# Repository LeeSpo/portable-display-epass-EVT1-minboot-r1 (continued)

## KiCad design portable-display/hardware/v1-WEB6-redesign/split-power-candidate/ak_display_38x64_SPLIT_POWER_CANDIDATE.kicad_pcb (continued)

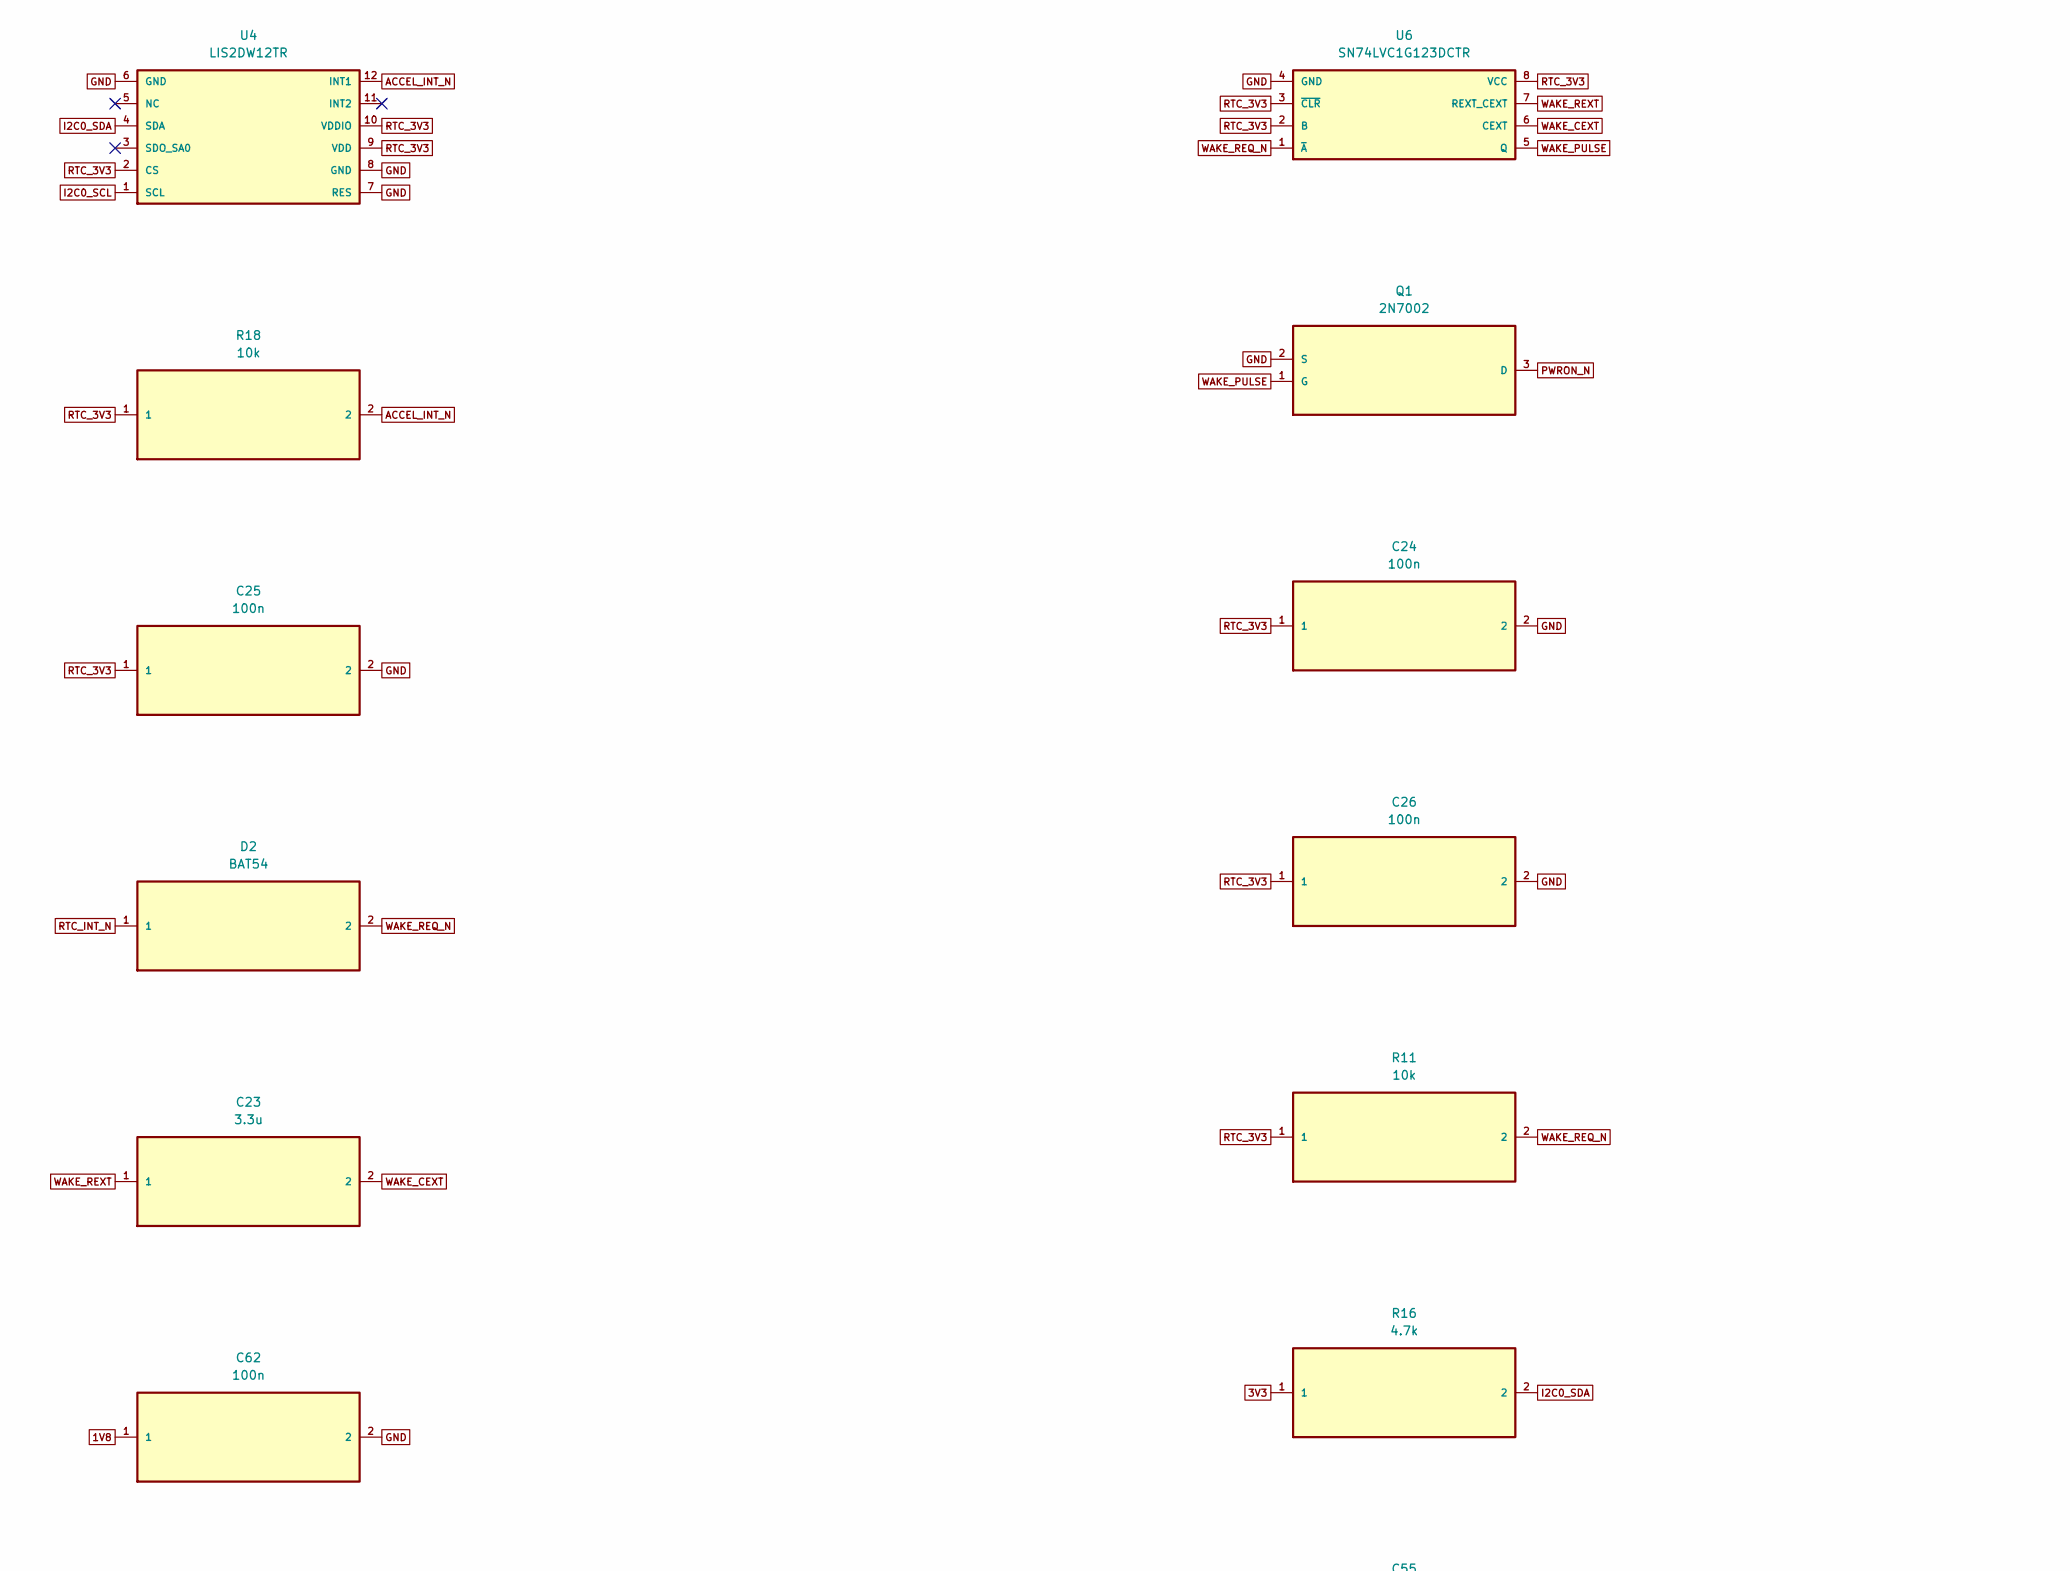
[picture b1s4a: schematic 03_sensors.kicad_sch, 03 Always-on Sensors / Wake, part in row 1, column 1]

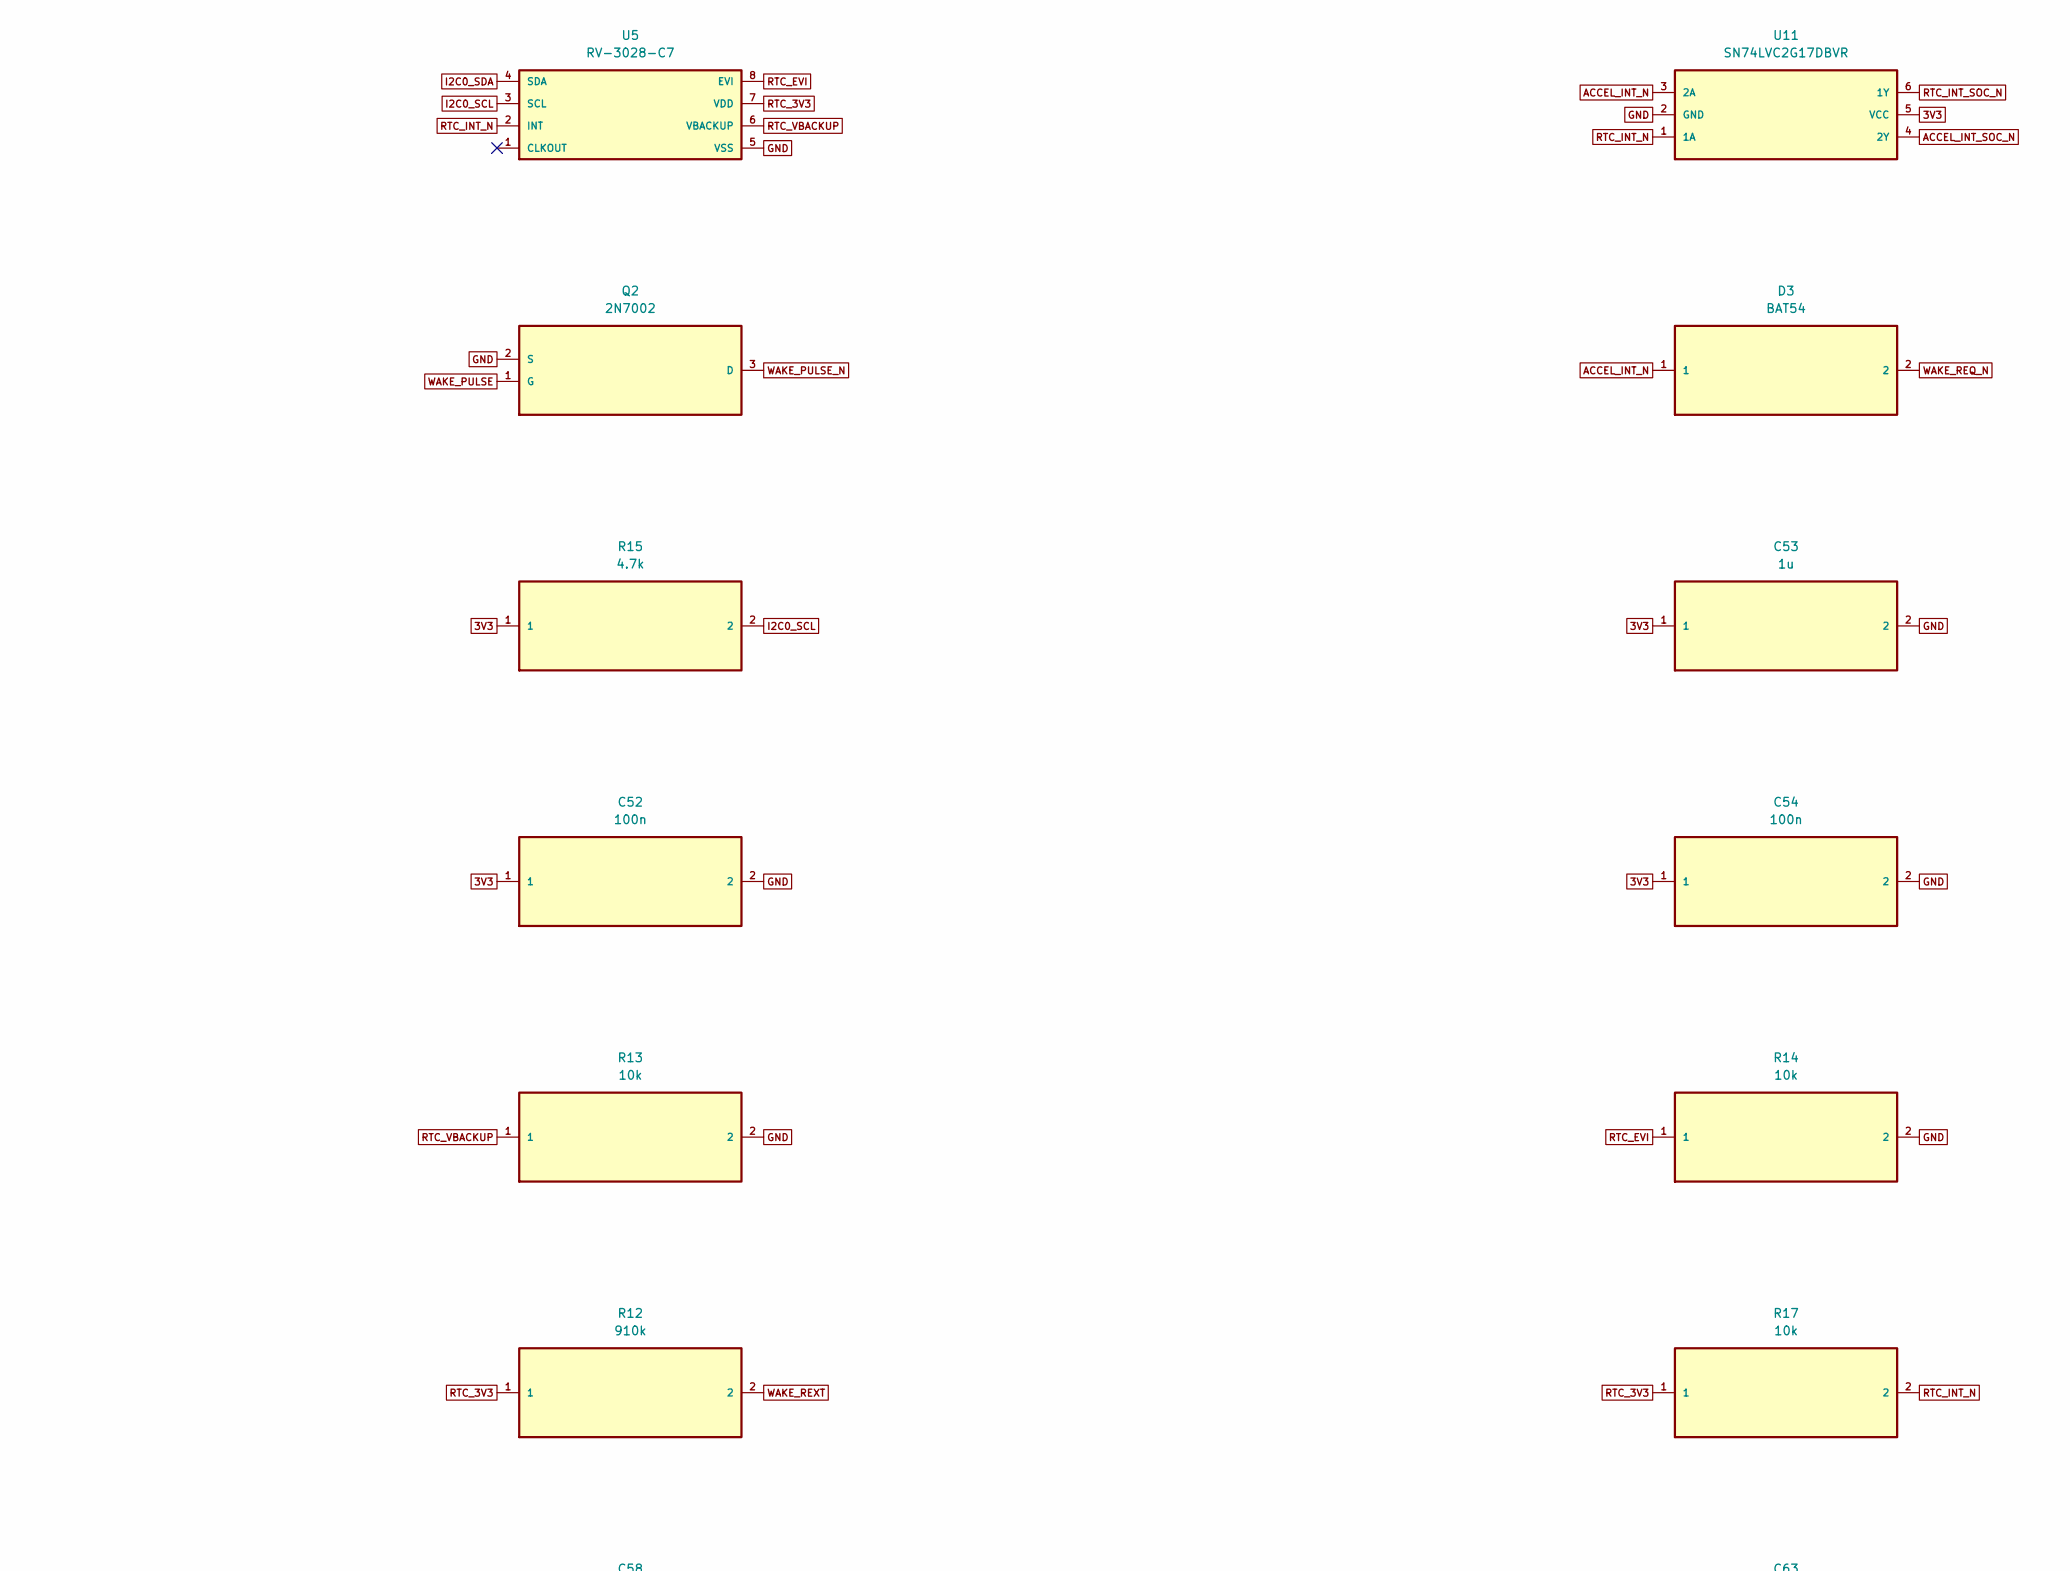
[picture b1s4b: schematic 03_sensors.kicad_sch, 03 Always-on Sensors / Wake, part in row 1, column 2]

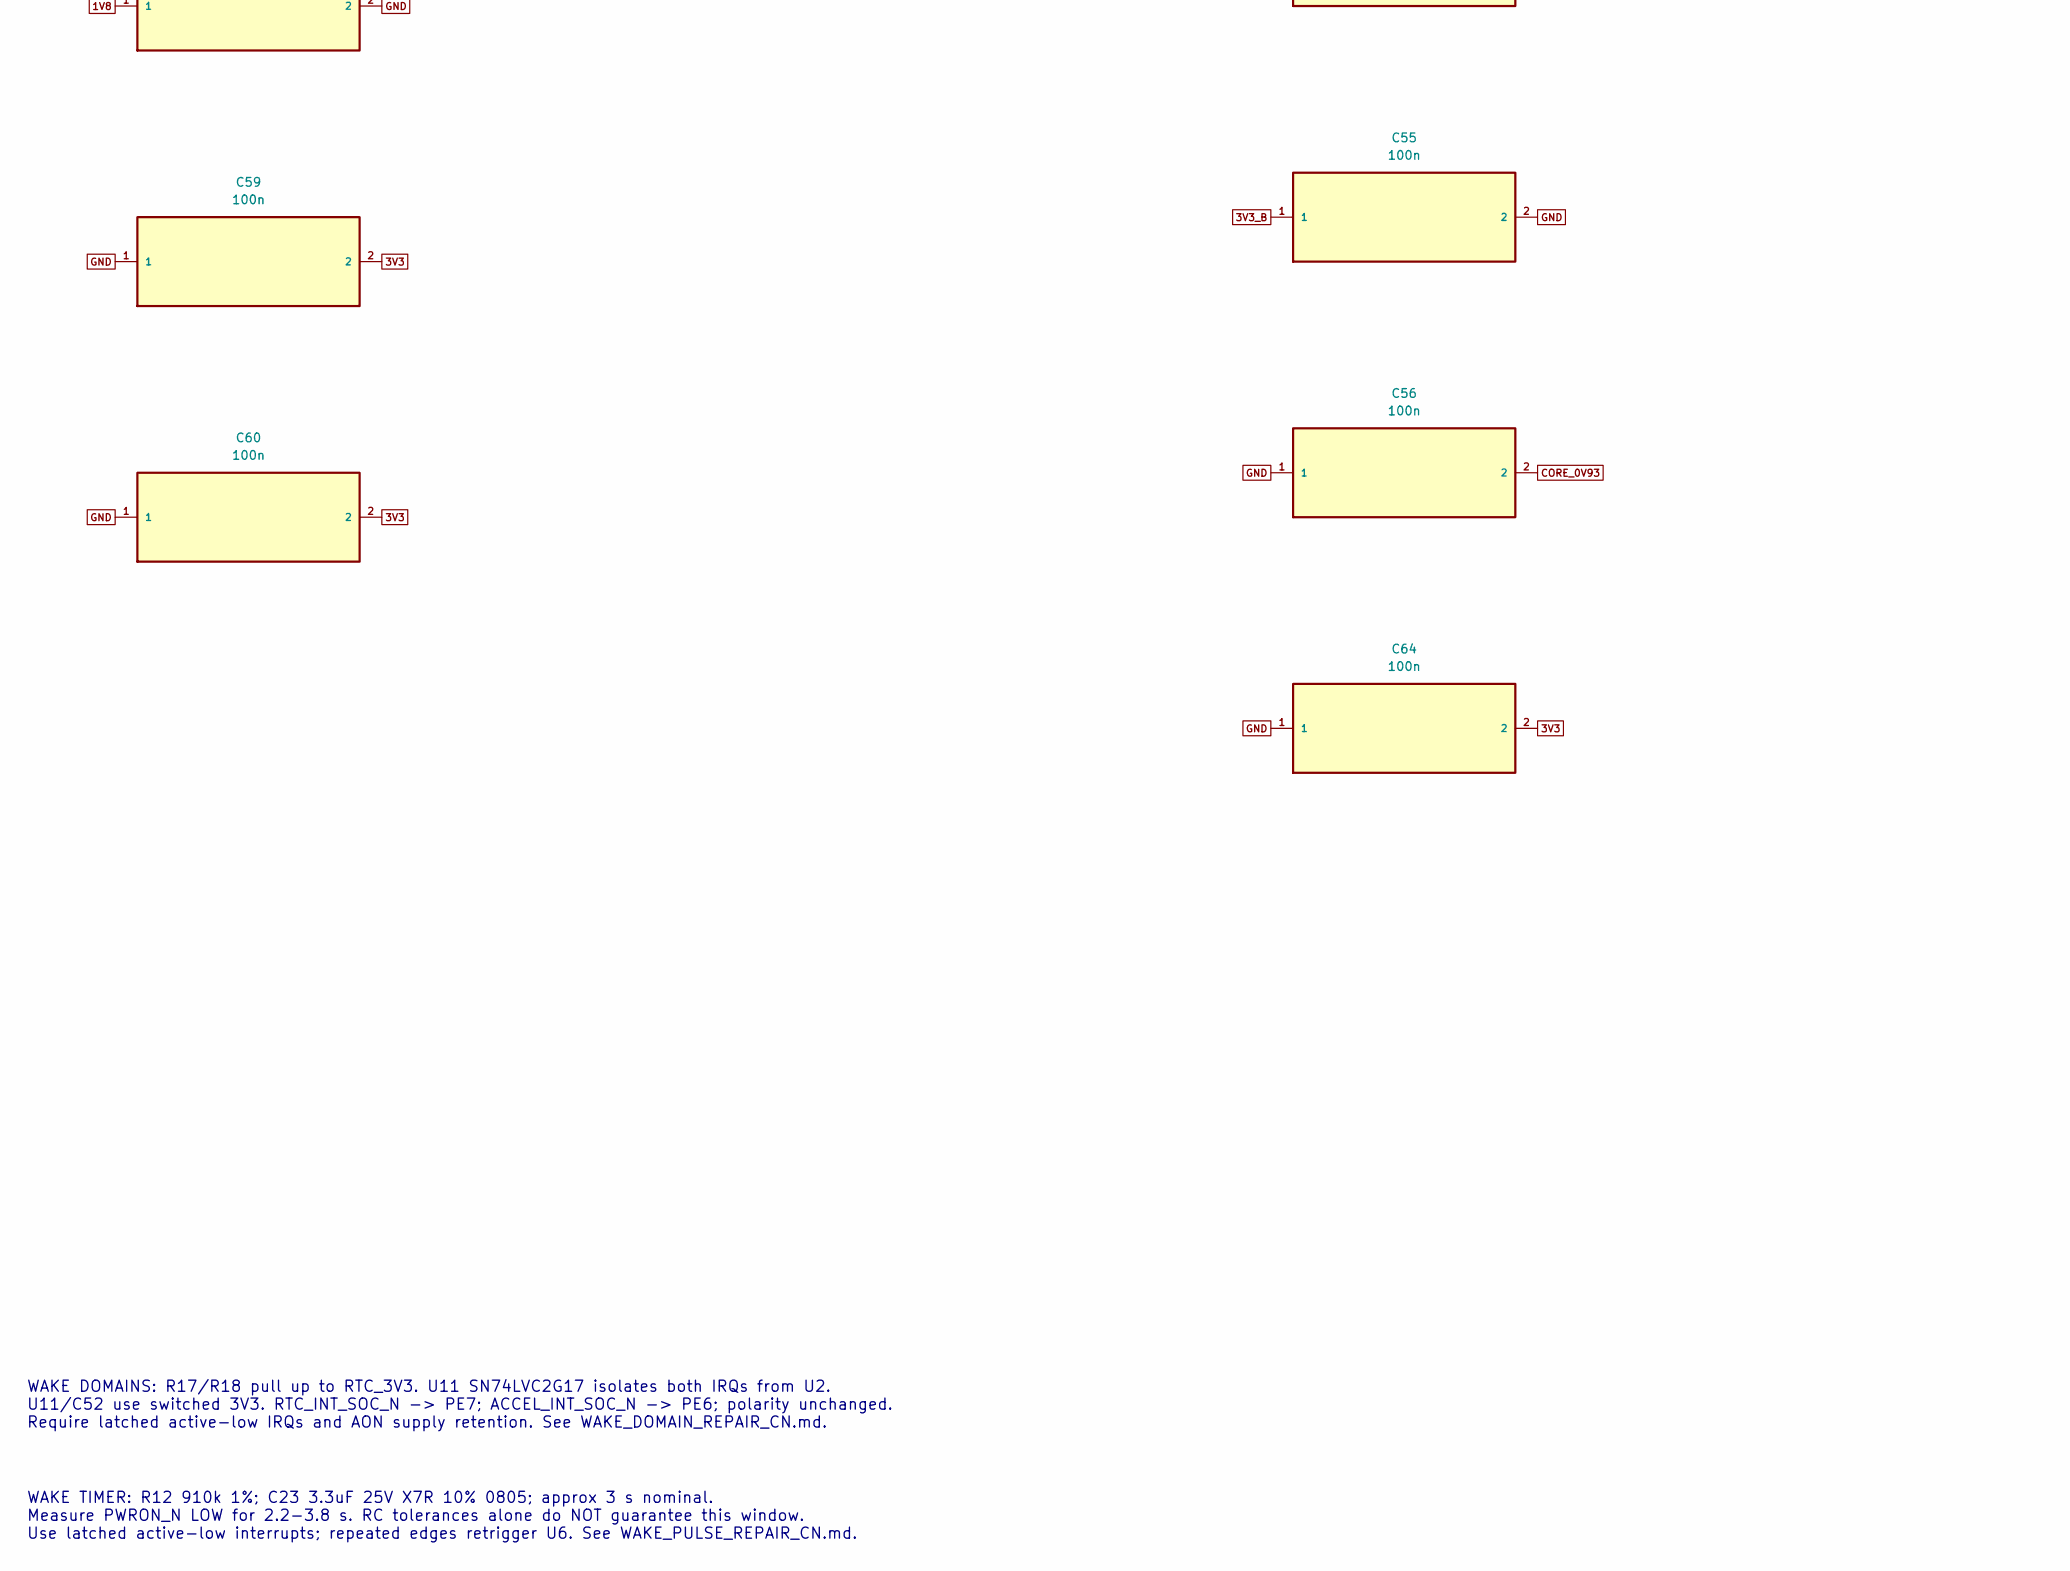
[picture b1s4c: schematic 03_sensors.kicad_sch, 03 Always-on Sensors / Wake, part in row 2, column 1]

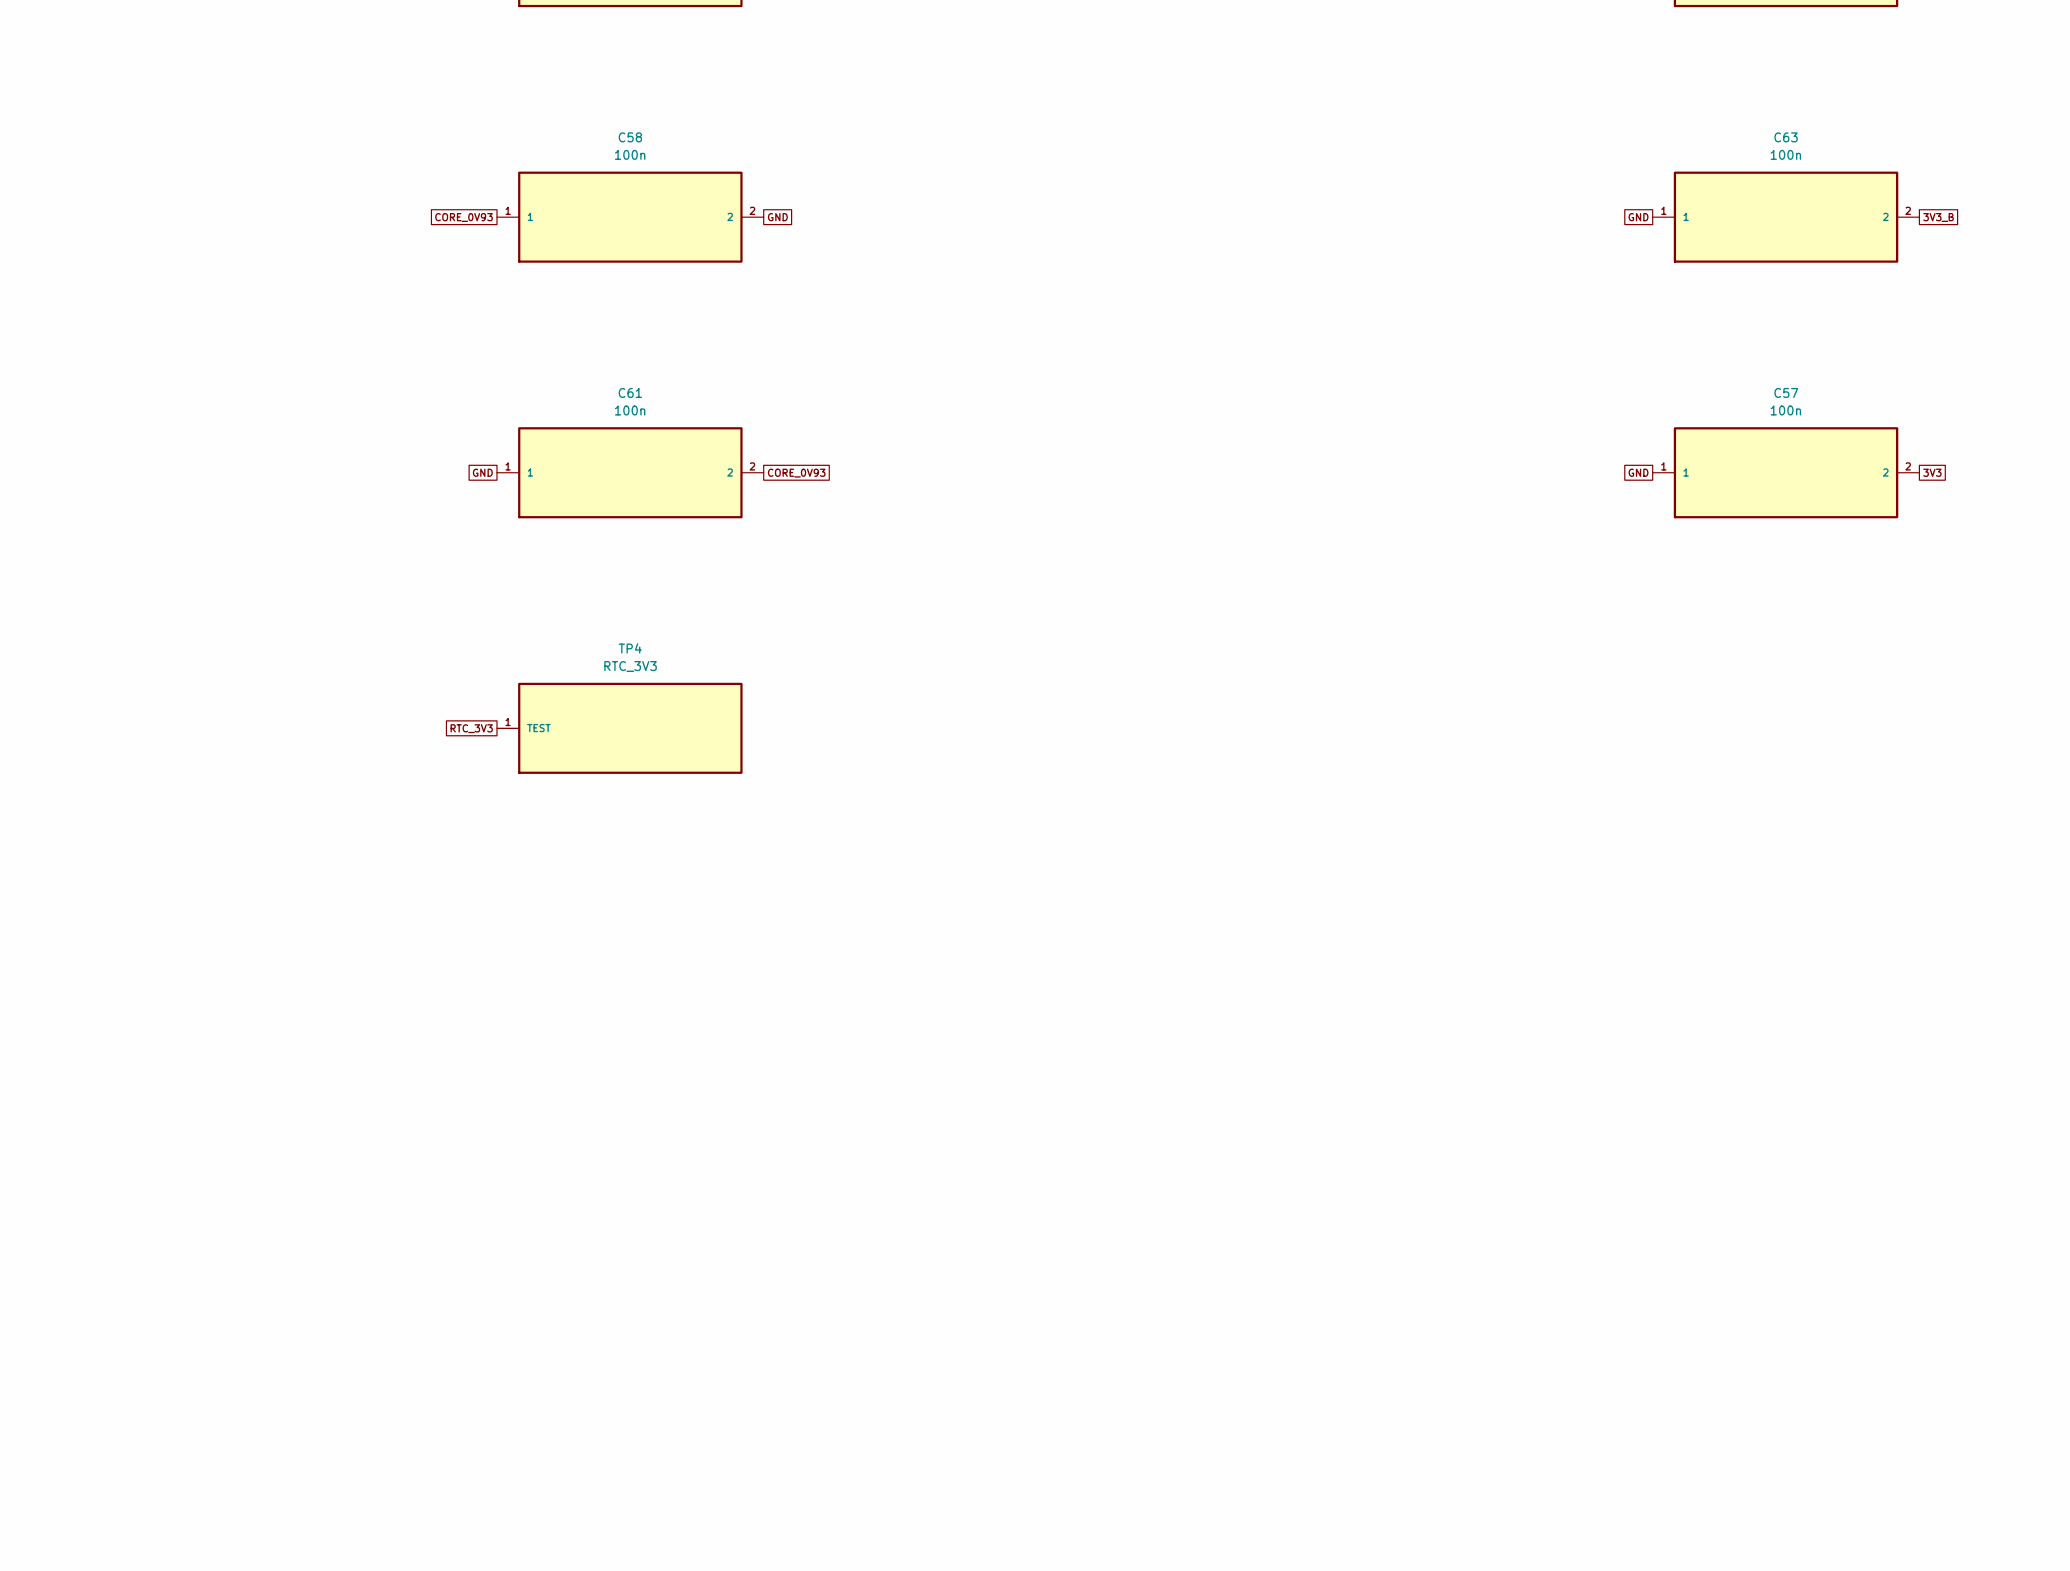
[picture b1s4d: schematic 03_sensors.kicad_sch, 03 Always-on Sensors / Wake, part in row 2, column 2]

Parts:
C23: 3.3u; C_0805_2012Metric; MPN TCC0805X7R335K250FT; LCSC C7393948
C24, C25, C26, C52: 100n; 0402; LCSC C1525
C53: 1u; 0402; MPN CL05A105KA5NQNC; LCSC C52923
C54, C55, C56, C57, C58, C59, C60, C61, C62, C63, C64: 100n; 0402; MPN CL05B104KO5NNNC; LCSC C1525
D2, D3: BAT54; D_SOD123; MPN BAT54W; LCSC C699107
Q1, Q2: 2N7002; SOT23-3; MPN 2N7002; LCSC C8545
R11, R13, R14, R17, R18: 10k; 0402; MPN 0402WGF1002TCE; LCSC C25744
R12: 910k; 0402; MPN AECR0402F910KK9; LCSC C352384
R15, R16: 4.7k; 0402; MPN 0402WGF4701TCE; LCSC C25900
TP4: RTC_3V3; TestPoint_Pad_D1.0mm
U4: LIS2DW12TR; LGA-12; MPN LIS2DW12TR; LCSC C189624
U5: RV-3028-C7; RTC-8; MPN RV-3028-C7-32.768kHz-1ppm-TA-QC; LCSC C3019759
U6: SN74LVC1G123DCTR; SN74LVC1G123_DCT8; MPN SN74LVC1G123DCTR; LCSC C123302
U11: SN74LVC2G17DBVR; SN74LVC2G17_DBV6; MPN SN74LVC2G17DBVR; LCSC C10429

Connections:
1V8: C62.1; also elsewhere on the board
3V3: C52.1, C53.1, C54.1, C57.2, C59.2, C60.2, C64.2, R15.1, R16.1, U11.5 (VCC); also elsewhere on the board
3V3_B: C55.1, C63.2; also elsewhere on the board
ACCEL_INT_N: D3.1, R18.2, U4.12 (INT1), U11.3 (2A)
ACCEL_INT_SOC_N: U11.4 (2Y); also elsewhere on the board
CORE_0V93: C56.2, C58.1, C61.2; also elsewhere on the board
GND: C24.2, C25.2, C26.2, C52.2, C53.2, C54.2, C55.2, C56.1, C57.1, C58.2, C59.1, C60.1, C61.1, C62.2, C63.1, C64.1, Q1.2 (S), Q2.2 (S), R13.2, R14.2, U4.6 (GND), U4.7 (RES), U4.8 (GND), U5.5 (VSS), U6.4 (GND), U11.2 (GND); also elsewhere on the board
I2C0_SCL: R15.2, U4.1 (SCL), U5.3 (SCL); also elsewhere on the board
I2C0_SDA: R16.2, U4.4 (SDA), U5.4 (SDA); also elsewhere on the board
PWRON_N: Q1.3 (D); also elsewhere on the board
RTC_3V3: C24.1, C25.1, C26.1, R11.1, R12.1, R17.1, R18.1, TP4.1 (TEST), U4.2 (CS), U4.9 (VDD), U4.10 (VDDIO), U5.7 (VDD), U6.2 (B), U6.3 (/CLR), U6.8 (VCC); also elsewhere on the board
RTC_EVI: R14.1, U5.8 (EVI)
RTC_INT_N: D2.1, R17.2, U5.2 (INT), U11.1 (1A)
RTC_INT_SOC_N: U11.6 (1Y); also elsewhere on the board
RTC_VBACKUP: R13.1, U5.6 (VBACKUP)
WAKE_CEXT: C23.2, U6.6 (CEXT)
WAKE_PULSE: Q1.1 (G), Q2.1 (G), U6.5 (Q)
WAKE_PULSE_N: Q2.3 (D); also elsewhere on the board
WAKE_REQ_N: D2.2, D3.2, R11.2, U6.1 (/A)
WAKE_REXT: C23.1, R12.2, U6.7 (REXT_CEXT)

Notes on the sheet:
WAKE DOMAINS: R17/R18 pull up to RTC_3V3. U11 SN74LVC2G17 isolates both IRQs from U2. U11/C52 use switched 3V3. RTC_INT_SOC_N -> PE7; ACCEL_INT_SOC_N -> PE6; polarity unchanged. Require latched active-low IRQs and AON supply retention. See WAKE_DOMAIN_REPAIR_CN.md.
WAKE TIMER: R12 910k 1%; C23 3.3uF 25V X7R 10% 0805; approx 3 s nominal. Measure PWRON_N LOW for 2.2-3.8 s. RC tolerances alone do NOT guarantee this window. Use latched active-low interrupts; repeated edges retrigger U6. See WAKE_PULSE_REPAIR_CN.md.
